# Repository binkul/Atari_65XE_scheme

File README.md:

# Atari_65XE_scheme
1) Improve GND project
2) Remove GTIA fixer (can be made over normal position)
3) 1 MB by Pasiu was added directy on board
4) Video is made by THT elements
5) Four OS
6) Up to eight Super Cartridges inside (MAC65, Action!, Basic XE, Basic XL, Atari Basic)

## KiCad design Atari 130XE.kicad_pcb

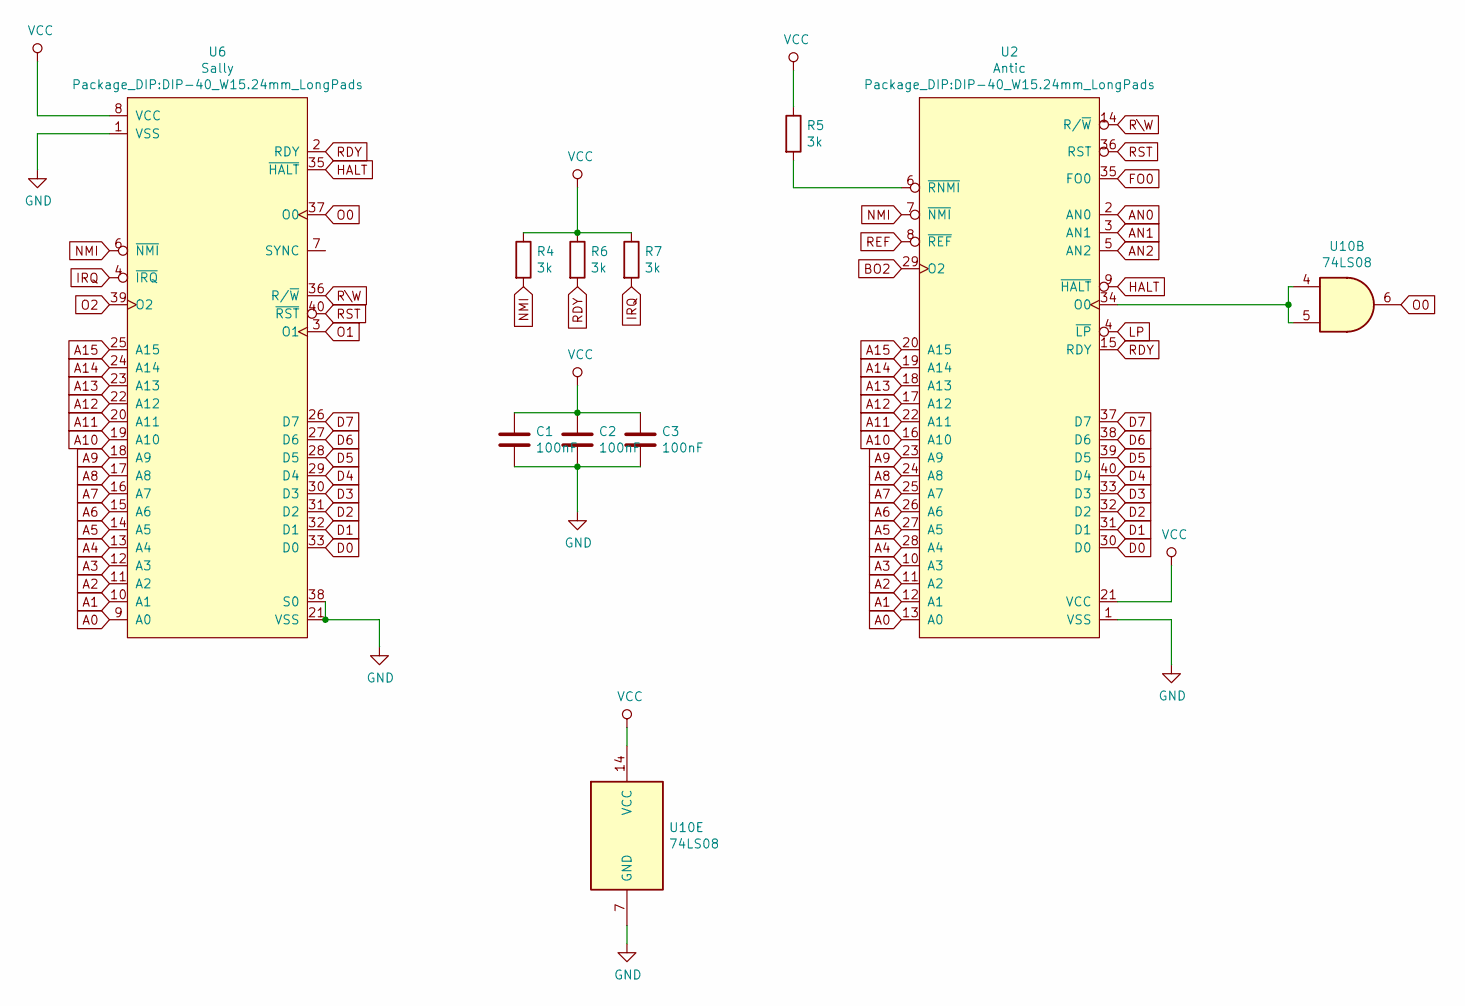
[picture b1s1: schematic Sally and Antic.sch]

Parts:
C1, C2, C3: 100nF; C_Disc_D5.0mm_W2.5mm_P5.00mm
R4, R5, R6, R7: 3k; R_Axial_DIN0207_L3.6mm_D2.2mm_P10.16mm_Horizontal
U2: Antic; DIP-40_W15.24mm_LongPads
U6: Sally; DIP-40_W15.24mm_LongPads
U10: 74LS08; DIP-14_W7.62mm_Socket_LongPads

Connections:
A0: U2.13 (A0), U6.9 (A0); also elsewhere on the board
A1: U2.12 (A1), U6.10 (A1); also elsewhere on the board
A2: U2.11 (A2), U6.11 (A2); also elsewhere on the board
A3: U2.10 (A3), U6.12 (A3); also elsewhere on the board
A4: U2.28 (A4), U6.13 (A4); also elsewhere on the board
A5: U2.27 (A5), U6.14 (A5); also elsewhere on the board
A6: U2.26 (A6), U6.15 (A6); also elsewhere on the board
A7: U2.25 (A7), U6.16 (A7); also elsewhere on the board
A8: U2.24 (A8), U6.17 (A8); also elsewhere on the board
A9: U2.23 (A9), U6.18 (A9); also elsewhere on the board
A10: U2.16 (A10), U6.19 (A10); also elsewhere on the board
A11: U2.22 (A11), U6.20 (A11); also elsewhere on the board
A12: U2.17 (A12), U6.22 (A12); also elsewhere on the board
A13: U2.18 (A13), U6.23 (A13); also elsewhere on the board
A14: U2.19 (A14), U6.24 (A14); also elsewhere on the board
A15: U2.20 (A15), U6.25 (A15); also elsewhere on the board
AN0: U2.2 (AN0); also elsewhere on the board
AN1: U2.3 (AN1); also elsewhere on the board
AN2: U2.5 (AN2); also elsewhere on the board
BO2: U2.29 (O2); also elsewhere on the board
D0: U2.30 (D0), U6.33 (D0); also elsewhere on the board
D1: U2.31 (D1), U6.32 (D1); also elsewhere on the board
D2: U2.32 (D2), U6.31 (D2); also elsewhere on the board
D3: U2.33 (D3), U6.30 (D3); also elsewhere on the board
D4: U2.40 (D4), U6.29 (D4); also elsewhere on the board
D5: U2.39 (D5), U6.28 (D5); also elsewhere on the board
D6: U2.38 (D6), U6.27 (D6); also elsewhere on the board
D7: U2.37 (D7), U6.26 (D7); also elsewhere on the board
FO0: U2.35 (FO0); also elsewhere on the board
GND: C1.2, C2.2, C3.2, U2.1 (VSS), U6.1 (VSS), U6.21 (VSS), U6.38 (S0), U10.7 (GND); also elsewhere on the board
HALT: U2.9 (~HALT), U6.35 (~HALT); also elsewhere on the board
IRQ: R7.2, U6.4 (~IRQ); also elsewhere on the board
LP: U2.4 (~LP); also elsewhere on the board
NMI: R4.2, U2.7 (~NMI), U6.6 (~NMI)
unnamed: R5.2, U2.6 (~RNMI)
unnamed: U2.34 (O0), U10.4, U10.5
O0: U6.37 (O0), U10.6; also elsewhere on the board
O1: U6.3 (O1); also elsewhere on the board
O2: U6.39 (O2); also elsewhere on the board
RDY: R6.2, U2.15 (RDY), U6.2 (RDY)
REF: U2.8 (~REF); also elsewhere on the board
RST: U2.36 (RST), U6.40 (~RST); also elsewhere on the board
R\W: U2.14 (R/~W), U6.36 (R/~W); also elsewhere on the board
VCC: C1.1, C2.1, C3.1, R4.1, R5.1, R6.1, R7.1, U2.21 (VCC), U6.8 (VCC), U10.14 (VCC); also elsewhere on the board

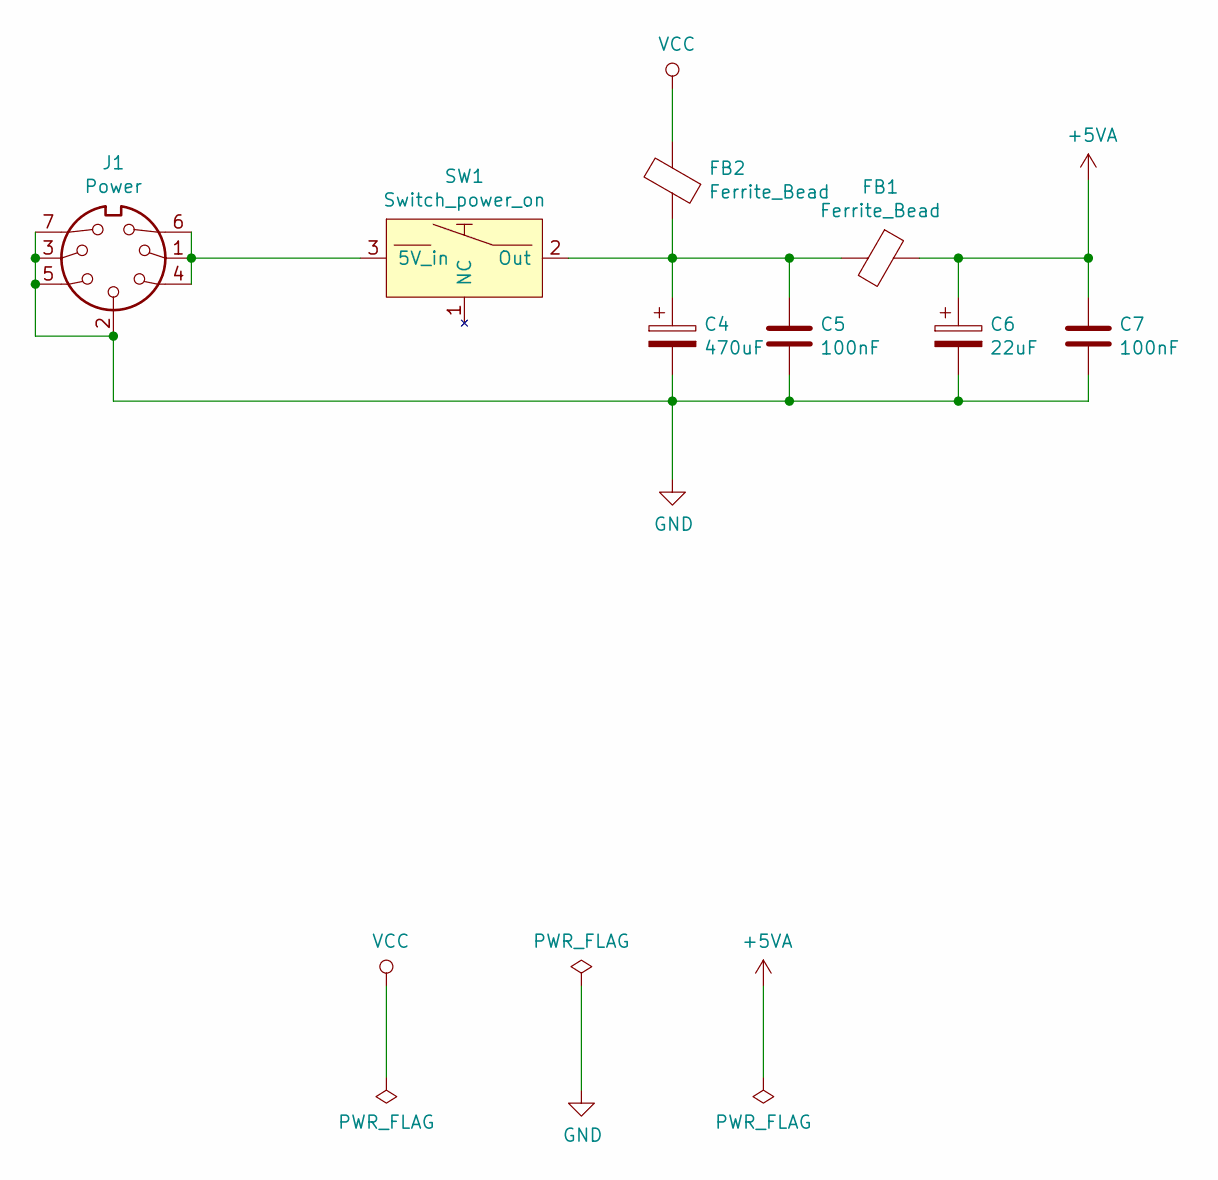
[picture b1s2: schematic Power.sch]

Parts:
C4: 470uF; CP_Radial_D10.0mm_P5.00mm
C5, C7: 100nF; C_Disc_D5.0mm_W2.5mm_P5.00mm
C6: 22uF; CP_Radial_D5.0mm_P2.00mm
FB1, FB2: Ferrite_Bead; L_Axial_L9.5mm_D4.0mm_P12.70mm_Horizontal_Fastron_SMCC
J1: Power; DIN_7_pin
SW1: Switch_power_on; Switch_ON-OFF

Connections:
+5VA: C6.1, C7.1, FB1.1; also elsewhere on the board
GND: C4.2, C5.2, C6.2, C7.2, J1.2, J1.3, J1.5, J1.7; also elsewhere on the board
unnamed 124: C4.1, C5.1, FB1.2, FB2.1, SW1.2 (Out); also elsewhere on the board
unnamed: J1.1, J1.4, J1.6, SW1.3 (5V_in)
VCC: FB2.2; also elsewhere on the board

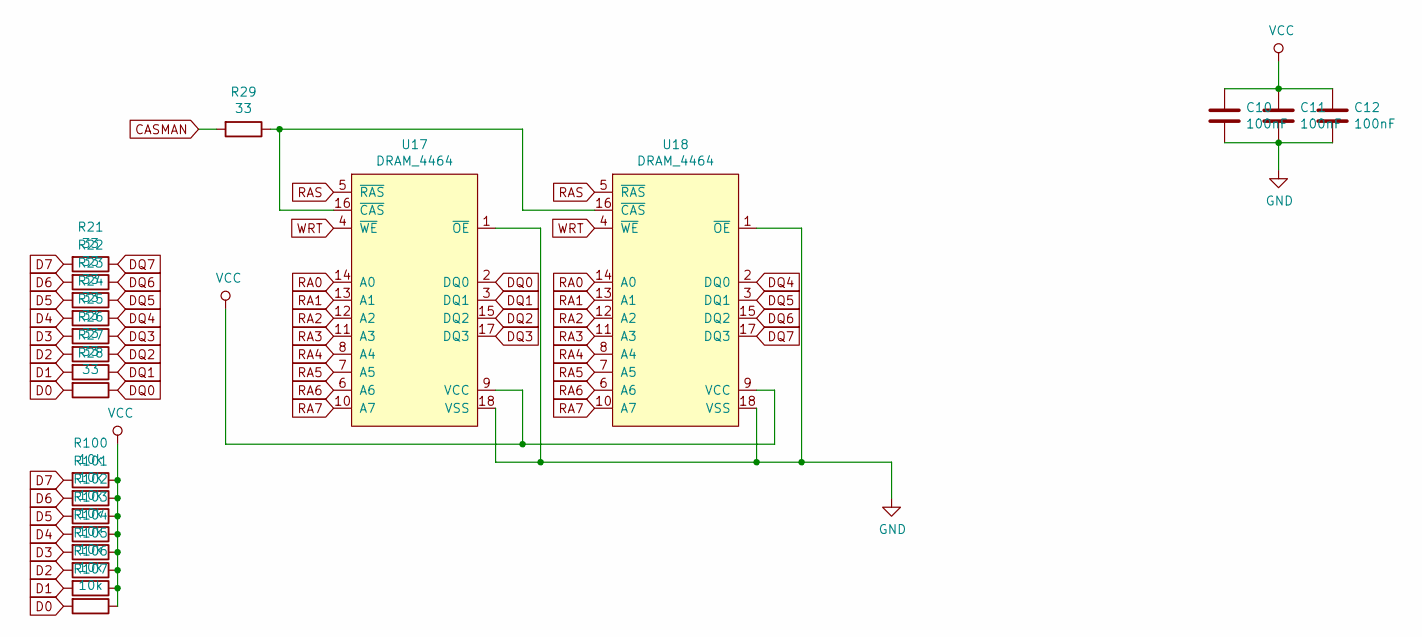
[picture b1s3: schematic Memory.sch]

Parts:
C10, C11, C12: 100nF; C_Disc_D5.0mm_W2.5mm_P5.00mm
R21, R22, R23, R24, R25, R26, R27, R28: 33; R_1206_3216Metric_Pad1.42x1.75mm_HandSolder
R29: 33; R_Axial_DIN0207_L3.6mm_D2.2mm_P10.16mm_Horizontal
R100, R101, R102, R103, R104, R105, R106, R107: 10k; R_1206_3216Metric_Pad1.42x1.75mm_HandSolder
U17, U18: DRAM_4464; DIP-18_W7.62mm_LongPads

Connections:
CASMAN: R29.2; also elsewhere on the board
D0: R28.2, R107.2; also elsewhere on the board
D1: R27.2, R106.2; also elsewhere on the board
D2: R26.2, R105.2; also elsewhere on the board
D3: R25.2, R104.2; also elsewhere on the board
D4: R24.2, R103.2; also elsewhere on the board
D5: R23.2, R102.2; also elsewhere on the board
D6: R22.2, R101.2; also elsewhere on the board
D7: R21.2, R100.2; also elsewhere on the board
DQ0: R28.1, U17.2 (DQ0); also elsewhere on the board
DQ1: R27.1, U17.3 (DQ1); also elsewhere on the board
DQ2: R26.1, U17.15 (DQ2); also elsewhere on the board
DQ3: R25.1, U17.17 (DQ3); also elsewhere on the board
DQ4: R24.1, U18.2 (DQ0); also elsewhere on the board
DQ5: R23.1, U18.3 (DQ1); also elsewhere on the board
DQ6: R22.1, U18.15 (DQ2); also elsewhere on the board
DQ7: R21.1, U18.17 (DQ3); also elsewhere on the board
GND: C10.2, C11.2, C12.2, U17.1 (~OE), U17.18 (VSS), U18.1 (~OE), U18.18 (VSS); also elsewhere on the board
unnamed: R29.1, U17.16 (~CAS), U18.16 (~CAS)
RA0: U17.14 (A0), U18.14 (A0); also elsewhere on the board
RA1: U17.13 (A1), U18.13 (A1); also elsewhere on the board
RA2: U17.12 (A2), U18.12 (A2); also elsewhere on the board
RA3: U17.11 (A3), U18.11 (A3); also elsewhere on the board
RA4: U17.8 (A4), U18.8 (A4); also elsewhere on the board
RA5: U17.7 (A5), U18.7 (A5); also elsewhere on the board
RA6: U17.6 (A6), U18.6 (A6); also elsewhere on the board
RA7: U17.10 (A7), U18.10 (A7); also elsewhere on the board
RAS: U17.5 (~RAS), U18.5 (~RAS); also elsewhere on the board
VCC: C10.1, C11.1, C12.1, R100.1, R101.1, R102.1, R103.1, R104.1, R105.1, R106.1, R107.1, U17.9 (VCC), U18.9 (VCC); also elsewhere on the board
WRT: U17.4 (~WE), U18.4 (~WE); also elsewhere on the board

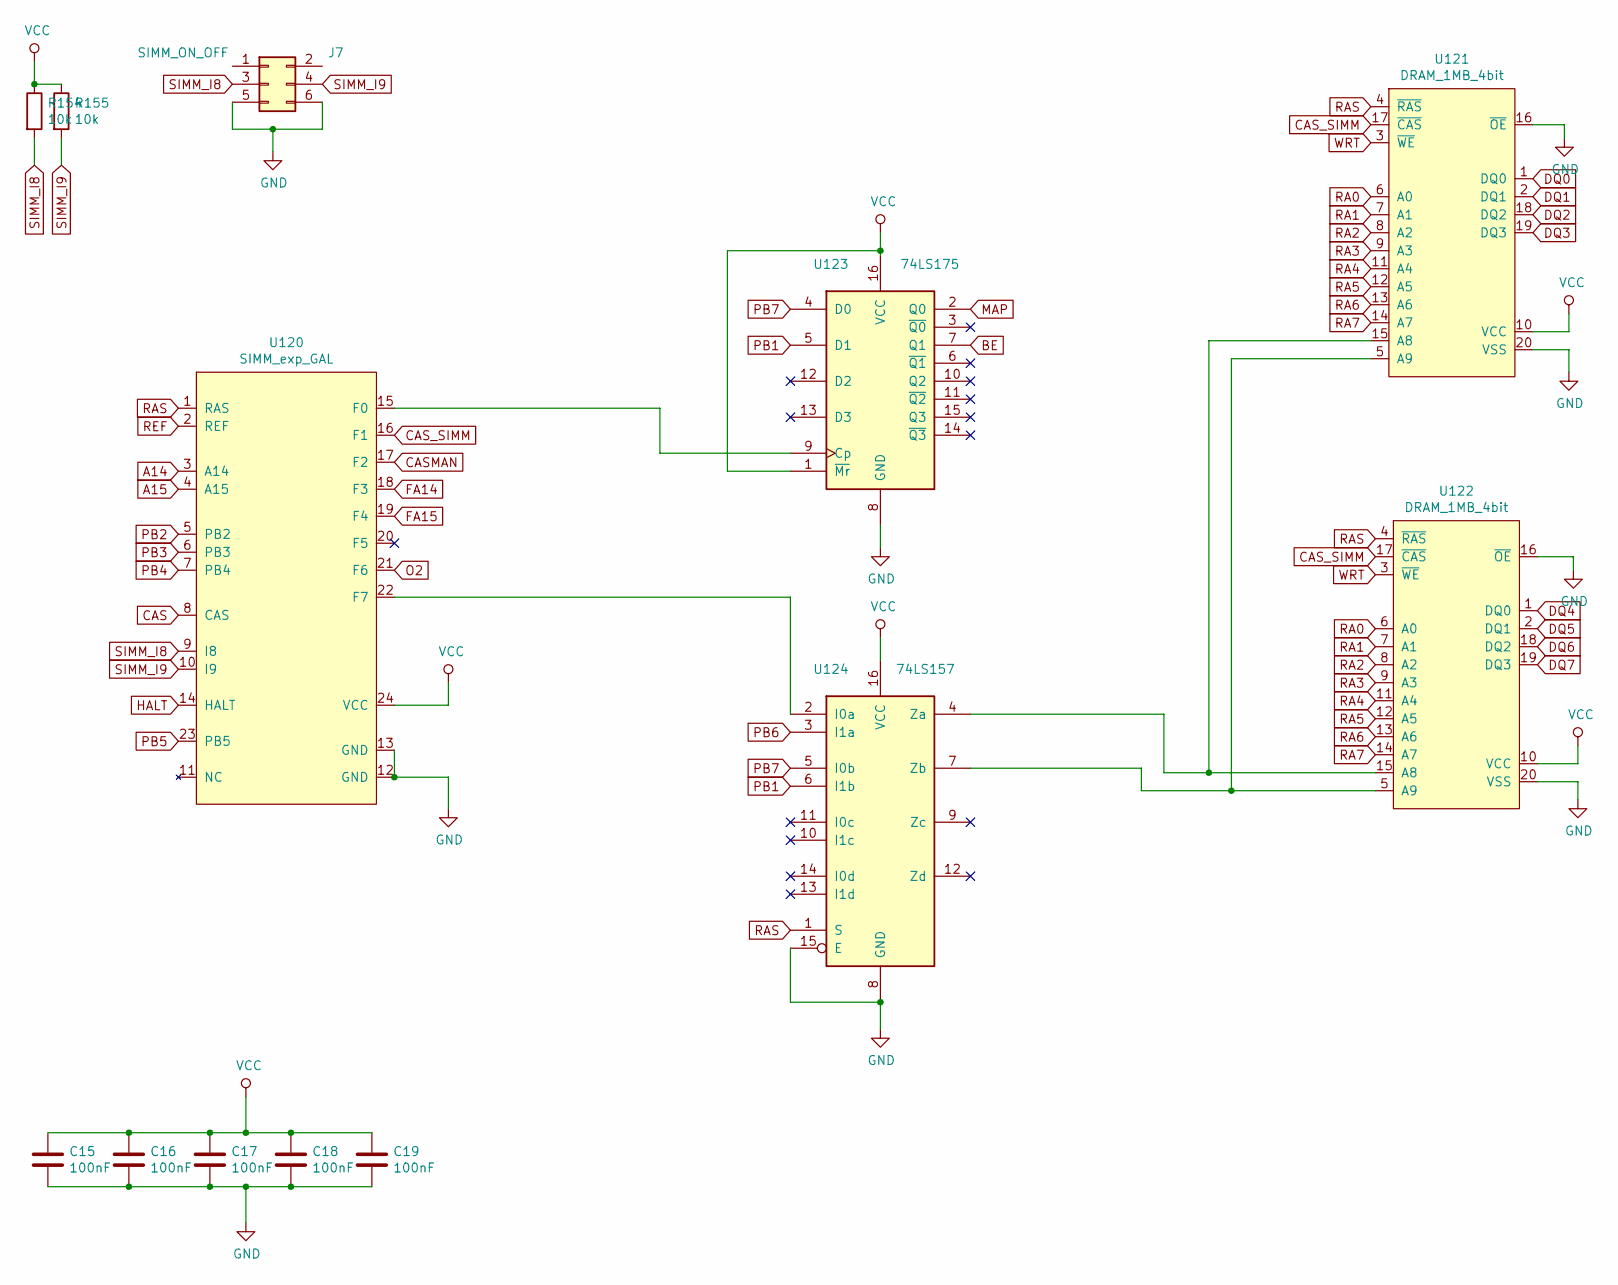
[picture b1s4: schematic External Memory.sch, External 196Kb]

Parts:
C15, C16, C17: 100nF; C_Disc_D5.0mm_W2.5mm_P5.00mm
C18, C19: 100nF; C_1206_3216Metric_Pad1.42x1.75mm_HandSolder
J7: SIMM_ON_OFF; PinHeader_2x03_P2.54mm_Vertical
R154, R155: 10k; R_1206_3216Metric_Pad1.42x1.75mm_HandSolder
U120: SIMM_exp_GAL; DIP-24_W7.62mm_Socket_LongPads
U121, U122: DRAM_1MB_4bit; SOJ-26
U123: 74LS175; SOIC-16_3.9x9.9mm_P1.27mm
U124: 74LS157; SOIC-16_3.9x9.9mm_P1.27mm

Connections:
A14: U120.3 (A14); also elsewhere on the board
A15: U120.4 (A15); also elsewhere on the board
BE: U123.7 (Q1); also elsewhere on the board
CAS: U120.8 (CAS); also elsewhere on the board
CASMAN: U120.17 (F2); also elsewhere on the board
CAS_SIMM: U120.16 (F1), U121.17 (~CAS), U122.17 (~CAS)
DQ0: U121.1 (DQ0); also elsewhere on the board
DQ1: U121.2 (DQ1); also elsewhere on the board
DQ2: U121.18 (DQ2); also elsewhere on the board
DQ3: U121.19 (DQ3); also elsewhere on the board
DQ4: U122.1 (DQ0); also elsewhere on the board
DQ5: U122.2 (DQ1); also elsewhere on the board
DQ6: U122.18 (DQ2); also elsewhere on the board
DQ7: U122.19 (DQ3); also elsewhere on the board
FA14: U120.18 (F3); also elsewhere on the board
FA15: U120.19 (F4); also elsewhere on the board
GND: C15.2, C16.2, C17.2, C18.2, C19.2, J7.5, J7.6, U120.12 (GND), U120.13 (GND), U121.16 (~OE), U121.20 (VSS), U122.16 (~OE), U122.20 (VSS), U123.8 (GND), U124.8 (GND), U124.15 (E); also elsewhere on the board
HALT: U120.14 (HALT); also elsewhere on the board
MAP: U123.2 (Q0); also elsewhere on the board
unnamed: U120.15 (F0), U123.9 (Cp)
unnamed: U120.22 (F7), U124.2 (I0a)
unnamed: U121.5 (A9), U122.5 (A9), U124.7 (Zb)
unnamed: U121.15 (A8), U122.15 (A8), U124.4 (Za)
O2: U120.21 (F6); also elsewhere on the board
PB1: U123.5 (D1), U124.6 (I1b); also elsewhere on the board
PB2: U120.5 (PB2); also elsewhere on the board
PB3: U120.6 (PB3); also elsewhere on the board
PB4: U120.7 (PB4); also elsewhere on the board
PB5: U120.23 (PB5); also elsewhere on the board
PB6: U124.3 (I1a); also elsewhere on the board
PB7: U123.4 (D0), U124.5 (I0b); also elsewhere on the board
RA0: U121.6 (A0), U122.6 (A0); also elsewhere on the board
RA1: U121.7 (A1), U122.7 (A1); also elsewhere on the board
RA2: U121.8 (A2), U122.8 (A2); also elsewhere on the board
RA3: U121.9 (A3), U122.9 (A3); also elsewhere on the board
RA4: U121.11 (A4), U122.11 (A4); also elsewhere on the board
RA5: U121.12 (A5), U122.12 (A5); also elsewhere on the board
RA6: U121.13 (A6), U122.13 (A6); also elsewhere on the board
RA7: U121.14 (A7), U122.14 (A7); also elsewhere on the board
RAS: U120.1 (RAS), U121.4 (~RAS), U122.4 (~RAS), U124.1 (S); also elsewhere on the board
REF: U120.2 (REF); also elsewhere on the board
SIMM_I8: J7.3, R154.2, U120.9 (I8)
SIMM_I9: J7.4, R155.2, U120.10 (I9)
VCC: C15.1, C16.1, C17.1, C18.1, C19.1, R154.1, R155.1, U120.24 (VCC), U121.10 (VCC), U122.10 (VCC), U123.1 (~Mr), U123.16 (VCC), U124.16 (VCC); also elsewhere on the board
WRT: U121.3 (~WE), U122.3 (~WE); also elsewhere on the board

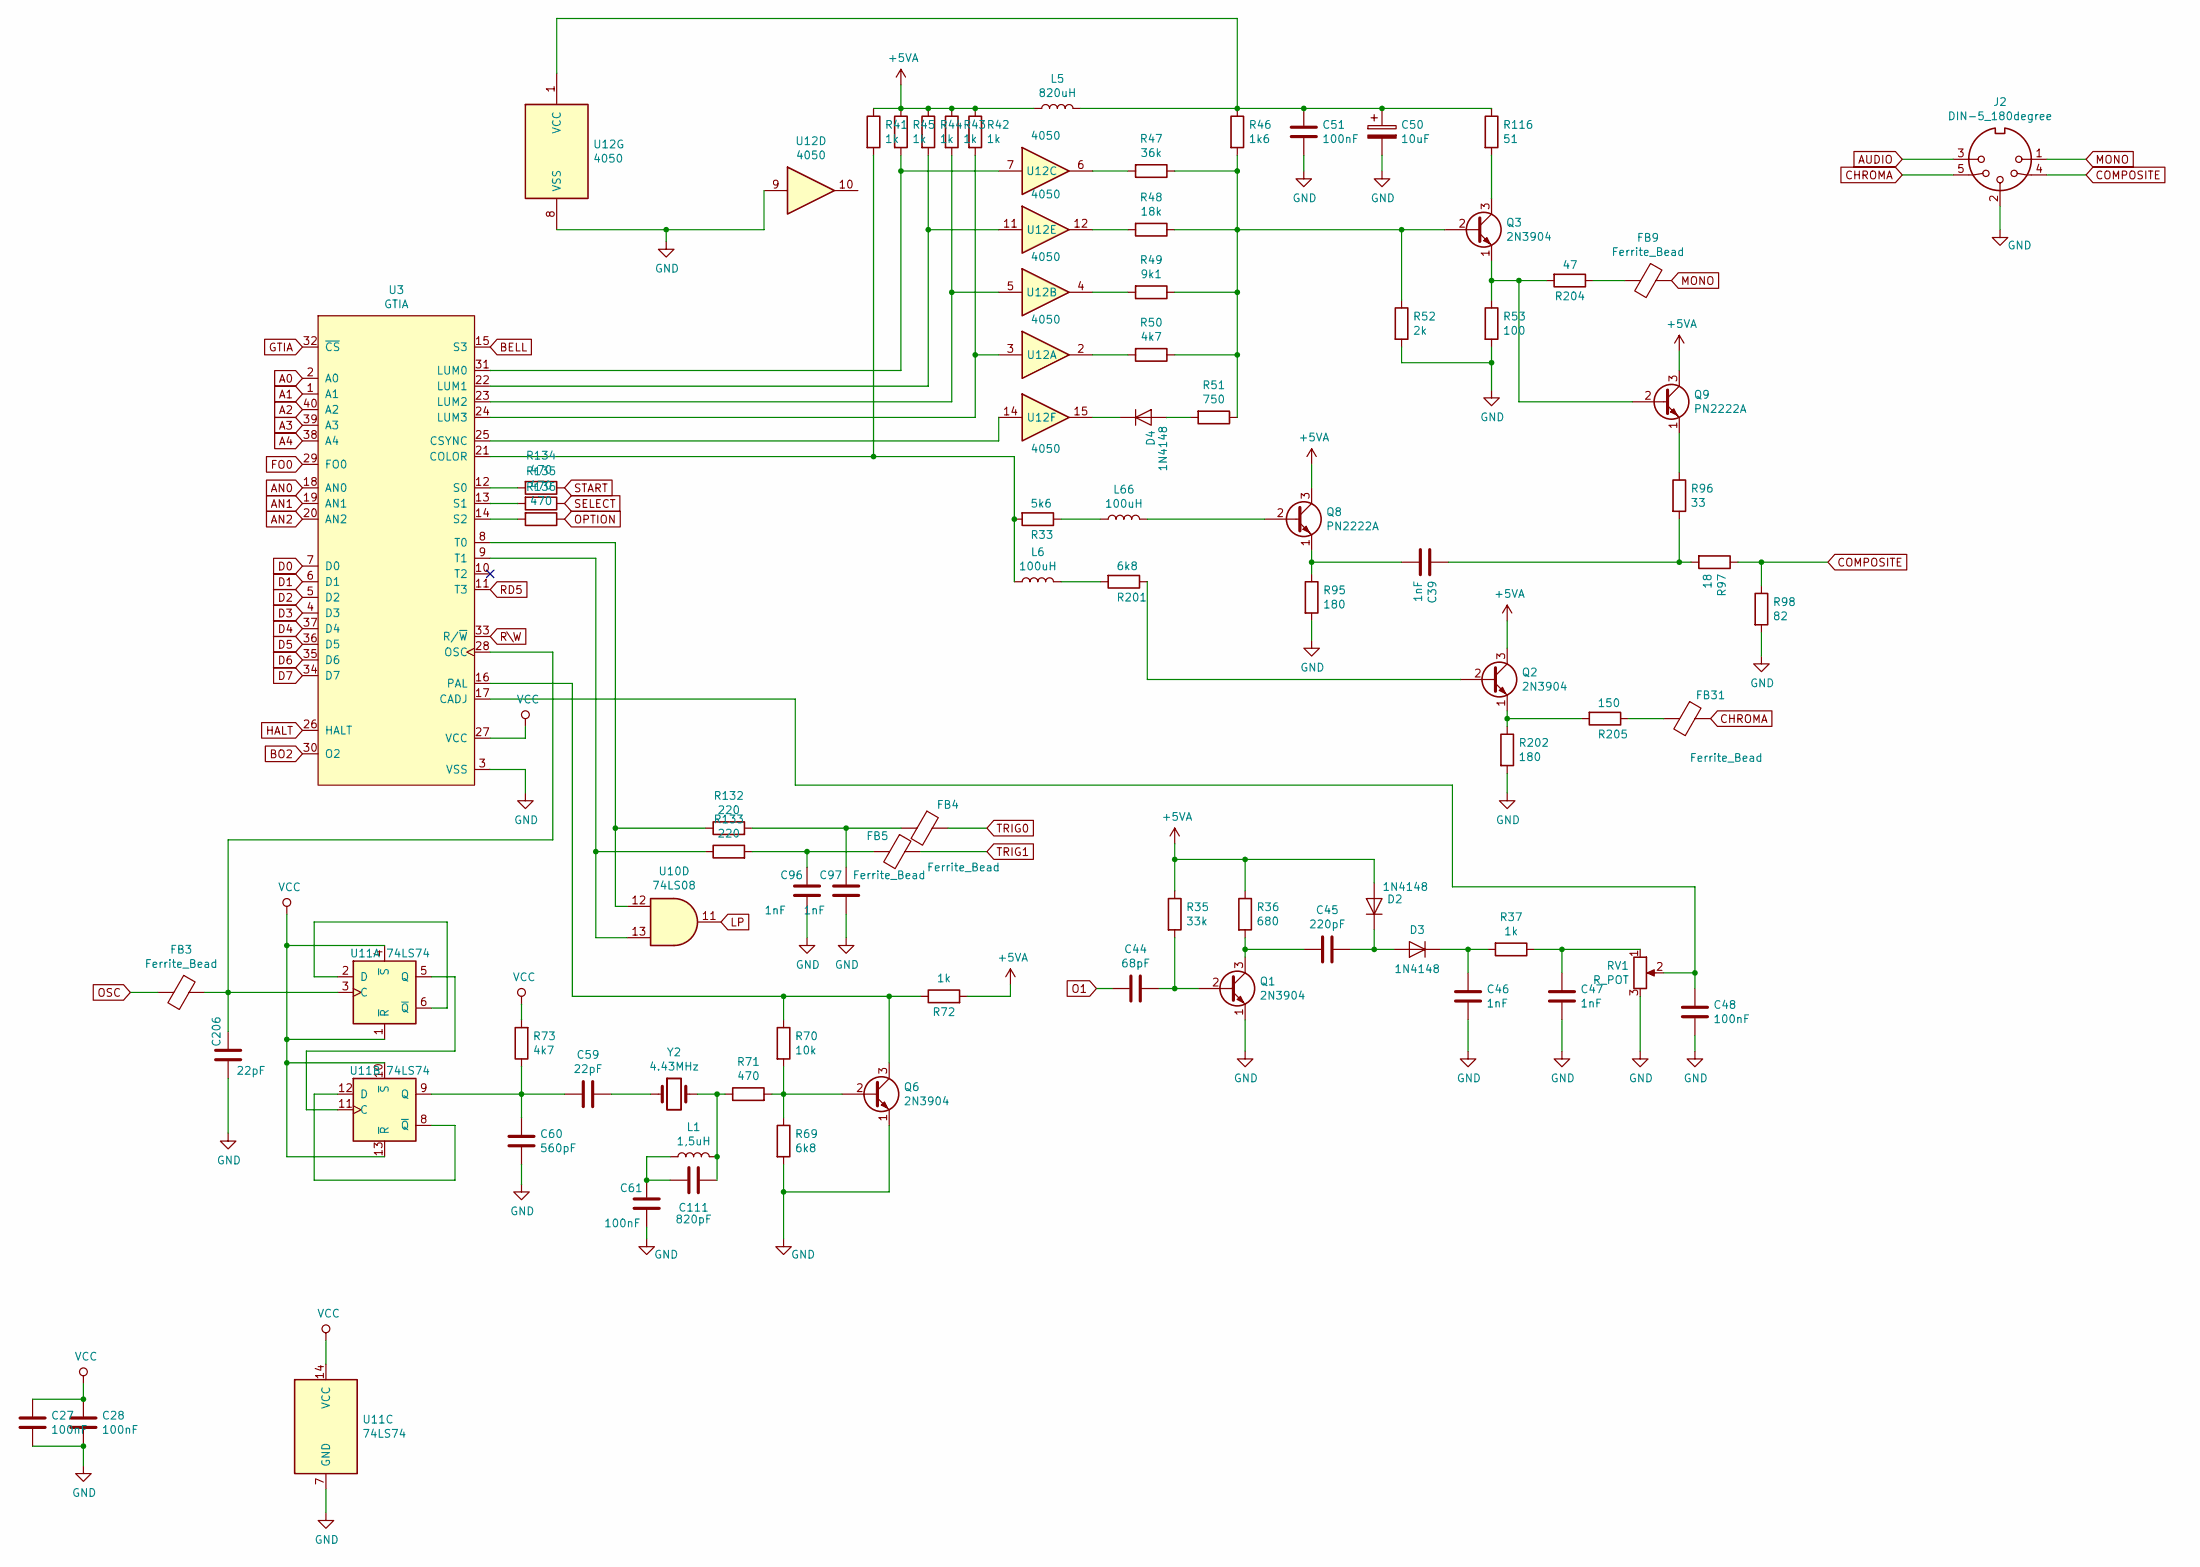
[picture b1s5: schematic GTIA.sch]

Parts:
C27, C28, C48, C51, C61: 100nF; C_Disc_D5.0mm_W2.5mm_P5.00mm
C39: 1nF; C_1206_3216Metric_Pad1.42x1.75mm_HandSolder
C44: 68pF; C_Disc_D3.0mm_W2.0mm_P2.50mm
C45: 220pF; C_Disc_D5.0mm_W2.5mm_P5.00mm
C46, C47, C96, C97: 1nF; C_Disc_D5.0mm_W2.5mm_P5.00mm
C50: 10uF; CP_Radial_D6.3mm_P2.50mm
C59, C206: 22pF; C_Disc_D5.0mm_W2.5mm_P5.00mm
C60: 560pF; C_Disc_D5.0mm_W2.5mm_P5.00mm
C111: 820pF; C_Disc_D5.0mm_W2.5mm_P5.00mm
D2, D3, D4: 1N4148; D_DO-34_SOD68_P10.16mm_Horizontal
FB3, FB4, FB5, FB9, FB31: Ferrite_Bead; L_Axial_L7.0mm_D3.3mm_P10.16mm_Horizontal_Fastron_MICC
J2: DIN-5_180degree; DIN_5_pin
L1: 1,5uH; L_Axial_L5.3mm_D2.2mm_P10.16mm_Horizontal_Vishay_IM-1
L5: 820uH; L_Axial_L5.3mm_D2.2mm_P10.16mm_Horizontal_Vishay_IM-1
L6, L66: 100uH; L_Axial_L5.3mm_D2.2mm_P10.16mm_Horizontal_Vishay_IM-1
Q1, Q2, Q3, Q6: 2N3904; TO-92_Inline
Q8, Q9: PN2222A; TO-92_Inline
R33: 5k6; R_Axial_DIN0207_L3.6mm_D2.2mm_P10.16mm_Horizontal
R35: 33k; R_Axial_DIN0207_L3.6mm_D2.2mm_P10.16mm_Horizontal
R36: 680; R_Axial_DIN0207_L3.6mm_D2.2mm_P10.16mm_Horizontal
R37, R41, R42, R43, R44, R45, R72: 1k; R_Axial_DIN0207_L3.6mm_D2.2mm_P10.16mm_Horizontal
R46: 1k6; R_Axial_DIN0207_L3.6mm_D2.2mm_P10.16mm_Horizontal
R47: 36k; R_Axial_DIN0207_L3.6mm_D2.2mm_P10.16mm_Horizontal
R48: 18k; R_Axial_DIN0207_L3.6mm_D2.2mm_P10.16mm_Horizontal
R49: 9k1; R_Axial_DIN0207_L3.6mm_D2.2mm_P10.16mm_Horizontal
R50, R73: 4k7; R_Axial_DIN0207_L3.6mm_D2.2mm_P10.16mm_Horizontal
R51: 750; R_Axial_DIN0207_L3.6mm_D2.2mm_P10.16mm_Horizontal
R52: 2k; R_Axial_DIN0207_L3.6mm_D2.2mm_P10.16mm_Horizontal
R53: 100; R_Axial_DIN0207_L3.6mm_D2.2mm_P10.16mm_Horizontal
R69, R201: 6k8; R_Axial_DIN0207_L3.6mm_D2.2mm_P10.16mm_Horizontal
R70: 10k; R_Axial_DIN0207_L3.6mm_D2.2mm_P10.16mm_Horizontal
R71: 470; R_Axial_DIN0207_L3.6mm_D2.2mm_P10.16mm_Horizontal
R95: 180; R_1206_3216Metric_Pad1.42x1.75mm_HandSolder
R96: 33; R_1206_3216Metric_Pad1.42x1.75mm_HandSolder
R97: 18; R_1206_3216Metric_Pad1.42x1.75mm_HandSolder
R98: 82; R_1206_3216Metric_Pad1.42x1.75mm_HandSolder
R116: 51; R_Axial_DIN0207_L3.6mm_D2.2mm_P10.16mm_Horizontal
R132, R133: 220; R_1206_3216Metric_Pad1.42x1.75mm_HandSolder
R134, R135, R136: 470; R_1206_3216Metric_Pad1.42x1.75mm_HandSolder
R202: 180; R_Axial_DIN0207_L3.6mm_D2.2mm_P10.16mm_Horizontal
R204: 47; R_Axial_DIN0207_L3.6mm_D2.2mm_P10.16mm_Horizontal
R205: 150; R_Axial_DIN0207_L3.6mm_D2.2mm_P10.16mm_Horizontal
RV1: R_POT; Potentiometer_ACP_CA9-V10_Vertical_Hole
U3: GTIA; DIP-40_W15.24mm_LongPads
U10: 74LS08; DIP-14_W7.62mm_Socket_LongPads
U11: 74LS74; DIP-14_W7.62mm_Socket
U12: 4050; DIP-16_W7.62mm_Socket
Y2: 4.43MHz; Crystal_HC18-U_Horizontal

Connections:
+5VA: D2.2 (A), L5.1, Q2.3 (C), Q8.3 (C), Q9.3 (C), R35.1, R36.1, R41.1, R42.1, R43.1, R44.1, R45.1, R72.2; also elsewhere on the board
A0: U3.2 (A0); also elsewhere on the board
A1: U3.1 (A1); also elsewhere on the board
A2: U3.40 (A2); also elsewhere on the board
A3: U3.39 (A3); also elsewhere on the board
A4: U3.38 (A4); also elsewhere on the board
AN0: U3.18 (AN0); also elsewhere on the board
AN1: U3.19 (AN1); also elsewhere on the board
AN2: U3.20 (AN2); also elsewhere on the board
AUDIO: J2.3; also elsewhere on the board
BELL: U3.15 (S3); also elsewhere on the board
BO2: U3.30 (O2); also elsewhere on the board
CHROMA: FB31.1, J2.5; also elsewhere on the board
COMPOSITE: J2.4, R97.1, R98.1; also elsewhere on the board
D0: U3.7 (D0); also elsewhere on the board
D1: U3.6 (D1); also elsewhere on the board
D2: U3.5 (D2); also elsewhere on the board
D3: U3.4 (D3); also elsewhere on the board
D4: U3.37 (D4); also elsewhere on the board
D5: U3.36 (D5); also elsewhere on the board
D6: U3.35 (D6); also elsewhere on the board
D7: U3.34 (D7); also elsewhere on the board
FO0: U3.29 (FO0); also elsewhere on the board
GND: C27.2, C28.2, C46.1, C47.1, C48.1, C50.2, C51.1, C60.2, C61.2, C96.2, C97.2, C206.2, J2.2, Q1.1 (E), Q6.1 (E), R52.2, R53.2, R69.2, R95.2, R98.2, R202.2, RV1.3, U3.3 (VSS), U11.7 (GND), U12.8 (VSS), U12.9; also elsewhere on the board
GTIA: U3.32 (~CS); also elsewhere on the board
HALT: U3.26 (HALT); also elsewhere on the board
LP: U10.11; also elsewhere on the board
MONO: FB9.1, J2.1; also elsewhere on the board
unnamed 104: C39.1, Q8.1 (E), R95.1; also elsewhere on the board
unnamed: C39.2, R96.2, R97.2
unnamed 108: C44.1, Q1.2 (B), R35.2; also elsewhere on the board
unnamed 109: C45.1, D2.1 (K), D3.2 (A); also elsewhere on the board
unnamed: C45.2, Q1.3 (C), R36.2
unnamed: C46.2, D3.1 (K), R37.2
unnamed: C47.2, R37.1, RV1.1
unnamed: C48.2, RV1.2, U3.17 (CADJ)
unnamed: C50.1, C51.2, L5.2, R46.1, R116.1, U12.1 (VCC)
unnamed 115: C59.1, Y2.1; also elsewhere on the board
unnamed: C59.2, C60.1, R73.1, U11.9 (Q)
unnamed: C96.1, FB5.2, R133.2
unnamed: C97.1, FB4.2, R132.2
unnamed 125: C111.1, L1.2, R71.1, Y2.2; also elsewhere on the board
unnamed: C61.1, C111.2, L1.1
unnamed: C206.1, FB3.1, U3.28 (OSC), U11.3 (C)
unnamed: D4.1 (K), U12.15
unnamed: D4.2 (A), R51.2
unnamed: FB9.2, R204.1
unnamed: FB31.2, R205.1
unnamed: L6.1, R33.2, R41.2, U3.21 (COLOR)
unnamed: L6.2, R201.2
unnamed: L66.1, R33.1
unnamed: L66.2, Q8.2 (B)
unnamed: Q2.1 (E), R202.1, R205.2
unnamed: Q2.2 (B), R201.1
unnamed: Q3.1 (E), Q9.2 (B), R53.1, R204.2
unnamed: Q3.2 (B), R46.2, R47.1, R48.1, R49.1, R50.1, R51.1, R52.1
unnamed: Q3.3 (C), R116.2
unnamed: Q6.2 (B), R69.1, R70.2, R71.2
unnamed: Q6.3 (C), R70.1, R72.1, U3.16 (PAL)
unnamed: Q9.1 (E), R96.1
unnamed: R42.2, U3.24 (LUM3), U12.3
unnamed: R43.2, U3.23 (LUM2), U12.5
unnamed: R44.2, U3.22 (LUM1), U12.11
unnamed: R45.2, U3.31 (LUM0), U12.7
unnamed: R47.2, U12.6
unnamed: R48.2, U12.12
unnamed: R49.2, U12.4
unnamed: R50.2, U12.2
unnamed: R132.1, U3.8 (T0), U10.12
unnamed: R133.1, U3.9 (T1), U10.13
unnamed: R134.2, U3.12 (S0)
unnamed: R135.2, U3.13 (S1)
unnamed: R136.2, U3.14 (S2)
unnamed: U11.2 (D), U11.6 (~Q)
unnamed: U11.5 (Q), U11.11 (C)
unnamed: U11.8 (~Q), U11.12 (D)
unnamed: U3.25 (CSYNC), U12.14
O1: C44.2; also elsewhere on the board
OPTION: R136.1; also elsewhere on the board
OSC: FB3.2; also elsewhere on the board
RD5: U3.11 (T3); also elsewhere on the board
R\W: U3.33 (R/~W); also elsewhere on the board
SELECT: R135.1; also elsewhere on the board
START: R134.1; also elsewhere on the board
TRIG0: FB4.1; also elsewhere on the board
TRIG1: FB5.1; also elsewhere on the board
VCC: C27.1, C28.1, R73.2, U3.27 (VCC), U11.1 (~R), U11.4 (~S), U11.10 (~S), U11.13 (~R), U11.14 (VCC); also elsewhere on the board

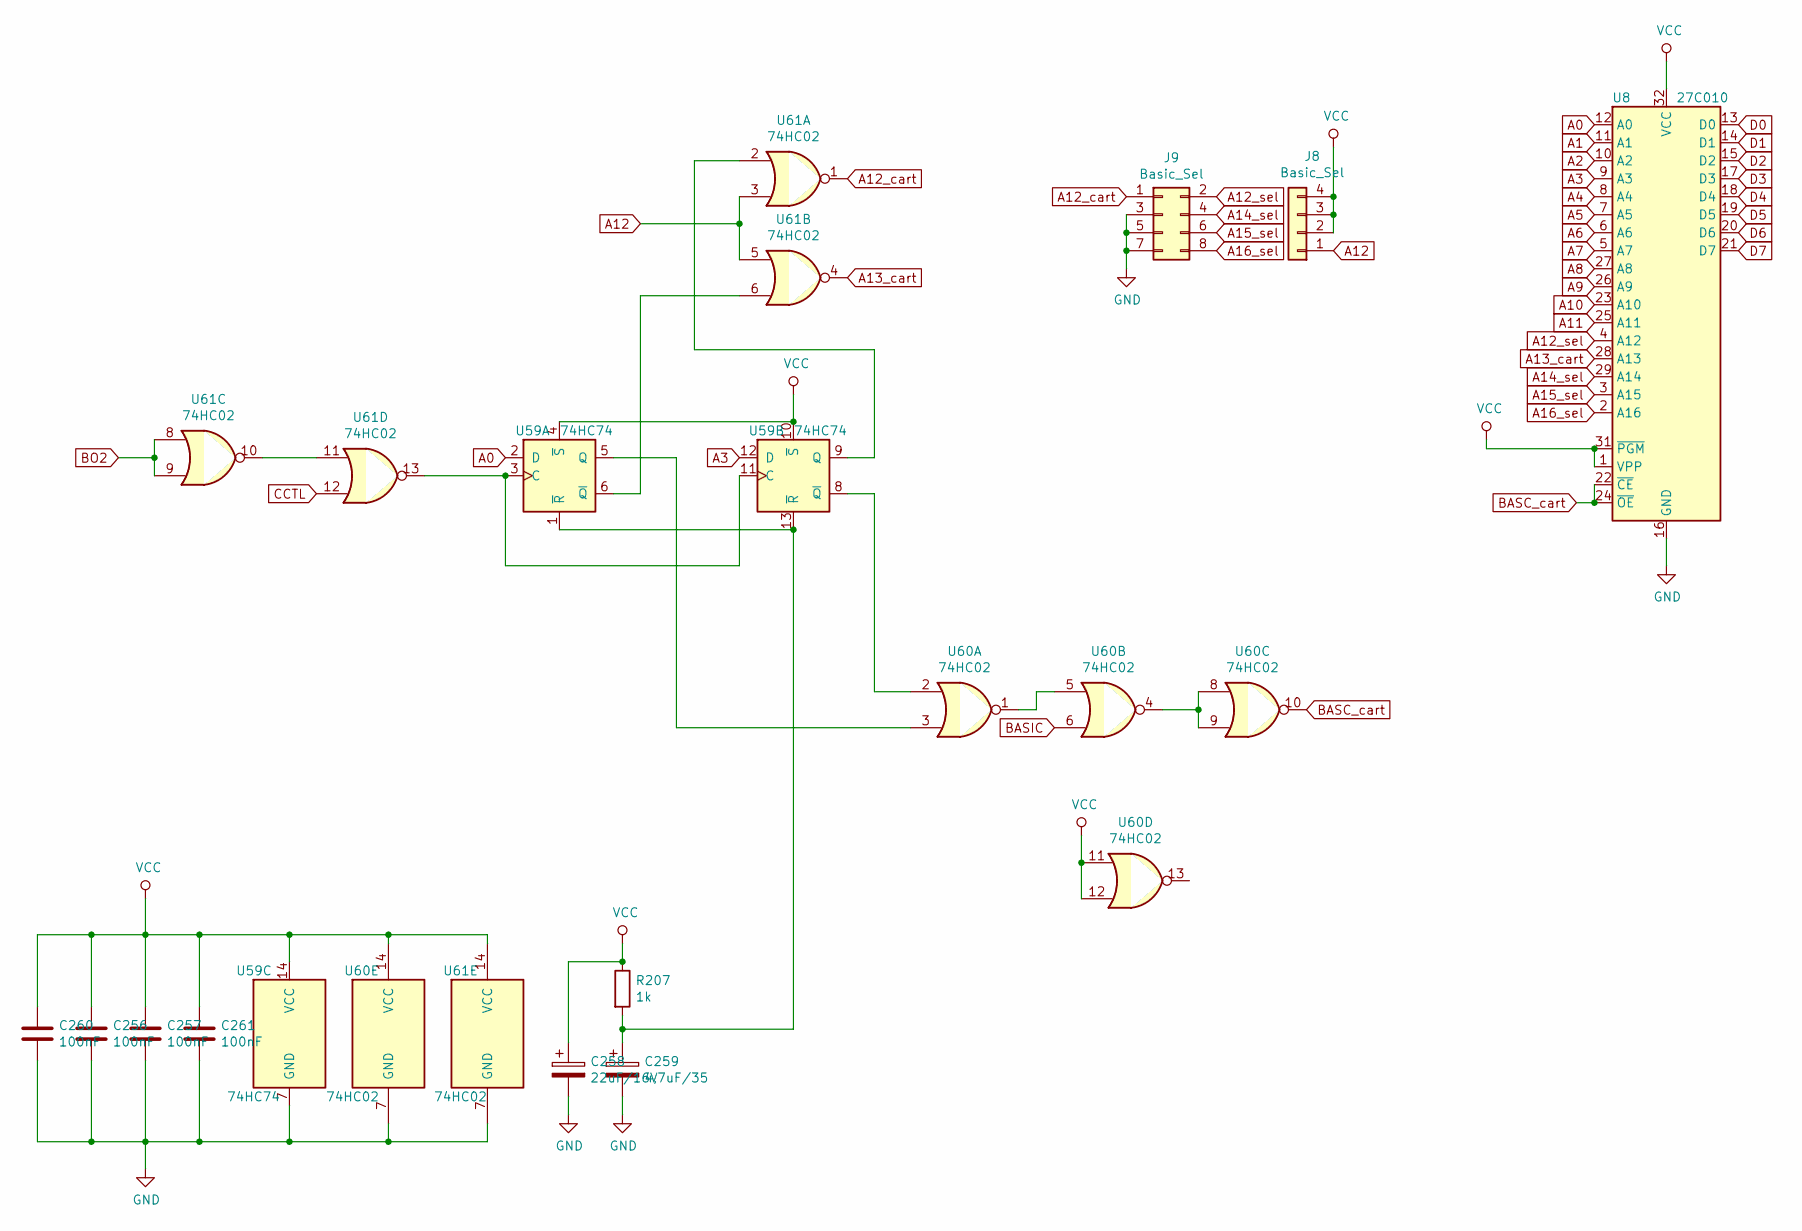
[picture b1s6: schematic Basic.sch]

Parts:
C256: 100nF; C_Disc_D6.0mm_W2.5mm_P5.00mm
C257, C260, C261: 100nF; C_1206_3216Metric_Pad1.42x1.75mm_HandSolder
C258: 22uF/16V; CP_Elec_4x5.3
C259: 4,7uF/35; CP_Elec_4x5.3
J8: Basic_Sel; PinHeader_1x04_P2.54mm_Vertical
J9: Basic_Sel; PinHeader_2x04_P2.54mm_Vertical
R207: 1k; R_1206_3216Metric_Pad1.42x1.75mm_HandSolder
U8: 27C010; DIP-32_W15.24mm_Socket_LongPads
U59: 74HC74; SOIC-14_3.9x8.7mm_P1.27mm
U60, U61: 74HC02; SOIC-14_3.9x8.7mm_P1.27mm

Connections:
A0: U8.12 (A0), U59.2 (D); also elsewhere on the board
A1: U8.11 (A1); also elsewhere on the board
A2: U8.10 (A2); also elsewhere on the board
A3: U8.9 (A3), U59.12 (D); also elsewhere on the board
A4: U8.8 (A4); also elsewhere on the board
A5: U8.7 (A5); also elsewhere on the board
A6: U8.6 (A6); also elsewhere on the board
A7: U8.5 (A7); also elsewhere on the board
A8: U8.27 (A8); also elsewhere on the board
A9: U8.26 (A9); also elsewhere on the board
A10: U8.23 (A10); also elsewhere on the board
A11: U8.25 (A11); also elsewhere on the board
A12: J8.1, U61.3, U61.5; also elsewhere on the board
A12_cart: J9.1, U61.1
A12_sel: J9.2, U8.4 (A12)
A13_cart: U8.28 (A13), U61.4
A14_sel: J9.4, U8.29 (A14)
A15_sel: J9.6, U8.3 (A15)
A16_sel: J9.8, U8.2 (A16)
BASC_cart: U8.22 (~CE), U8.24 (~OE), U60.10
BASIC: U60.6; also elsewhere on the board
BO2: U61.8, U61.9; also elsewhere on the board
CCTL: U61.12; also elsewhere on the board
D0: U8.13 (D0); also elsewhere on the board
D1: U8.14 (D1); also elsewhere on the board
D2: U8.15 (D2); also elsewhere on the board
D3: U8.17 (D3); also elsewhere on the board
D4: U8.18 (D4); also elsewhere on the board
D5: U8.19 (D5); also elsewhere on the board
D6: U8.20 (D6); also elsewhere on the board
D7: U8.21 (D7); also elsewhere on the board
GND: C256.2, C257.2, C258.2, C259.2, C260.2, C261.2, J9.3, J9.5, J9.7, U8.16 (GND), U59.7 (GND), U60.7 (GND), U61.7 (GND); also elsewhere on the board
unnamed: C259.1, R207.2, U59.1 (~R), U59.13 (~R)
unnamed: U59.5 (Q), U60.3
unnamed: U59.6 (~Q), U61.6
unnamed: U59.8 (~Q), U60.2
unnamed: U59.9 (Q), U61.2
unnamed: U59.3 (C), U59.11 (C), U61.13
unnamed: U60.1, U60.5
unnamed: U60.4, U60.8, U60.9
unnamed: U61.10, U61.11
VCC: C256.1, C257.1, C258.1, C260.1, C261.1, J8.2, J8.3, J8.4, R207.1, U8.1 (VPP), U8.31 (~PGM), U8.32 (VCC), U59.4 (~S), U59.10 (~S), U59.14 (VCC), U60.11, U60.12, U60.14 (VCC), U61.14 (VCC); also elsewhere on the board
